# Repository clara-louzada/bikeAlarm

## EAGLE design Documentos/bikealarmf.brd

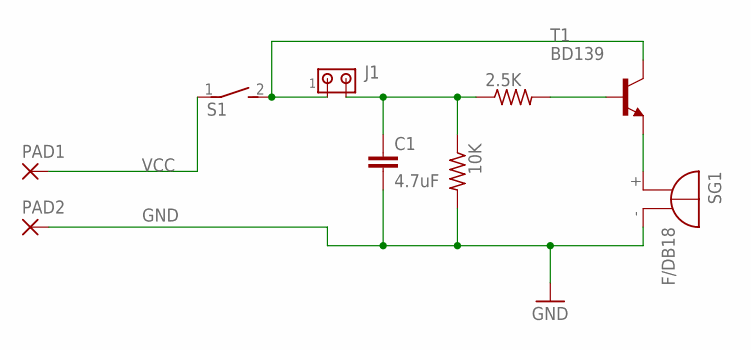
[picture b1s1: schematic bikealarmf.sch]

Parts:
2.5K, 10K: R-US_0204/7; 0204/7
C1: 4.7uF; C025-030X050
J1: MTA02-156; 1X2MTA
PAD1, PAD2: 2,15/1,0
S1: DS01E; DS-01
SG1: F/DB18
T1: BD139; TO126

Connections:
GND: 10K.2, C1.2, J1.1, PAD2.1, S1.2, SG1.-, T1.2 (C)
unnamed: SG1.+, T1.1 (E)
unnamed: 2.5K.2, T1.3 (B)
unnamed: 2.5K.1, 10K.1, C1.1, J1.2
VCC: PAD1.1, S1.1

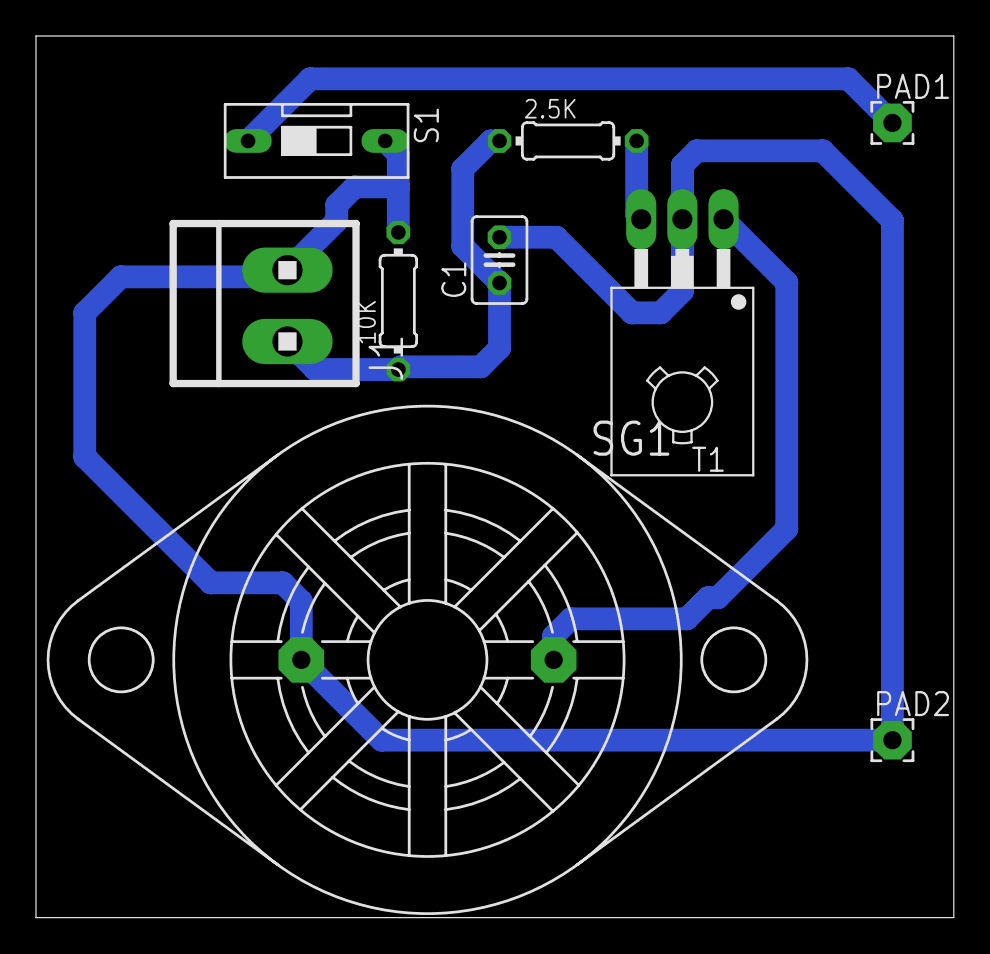
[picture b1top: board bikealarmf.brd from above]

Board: 2 copper layers, 51.0 x 49.0 mm, 9 parts (0 on the bottom side), 5 nets.

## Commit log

2019-03-10 Third commit
2019-03-19 Fourth commit
